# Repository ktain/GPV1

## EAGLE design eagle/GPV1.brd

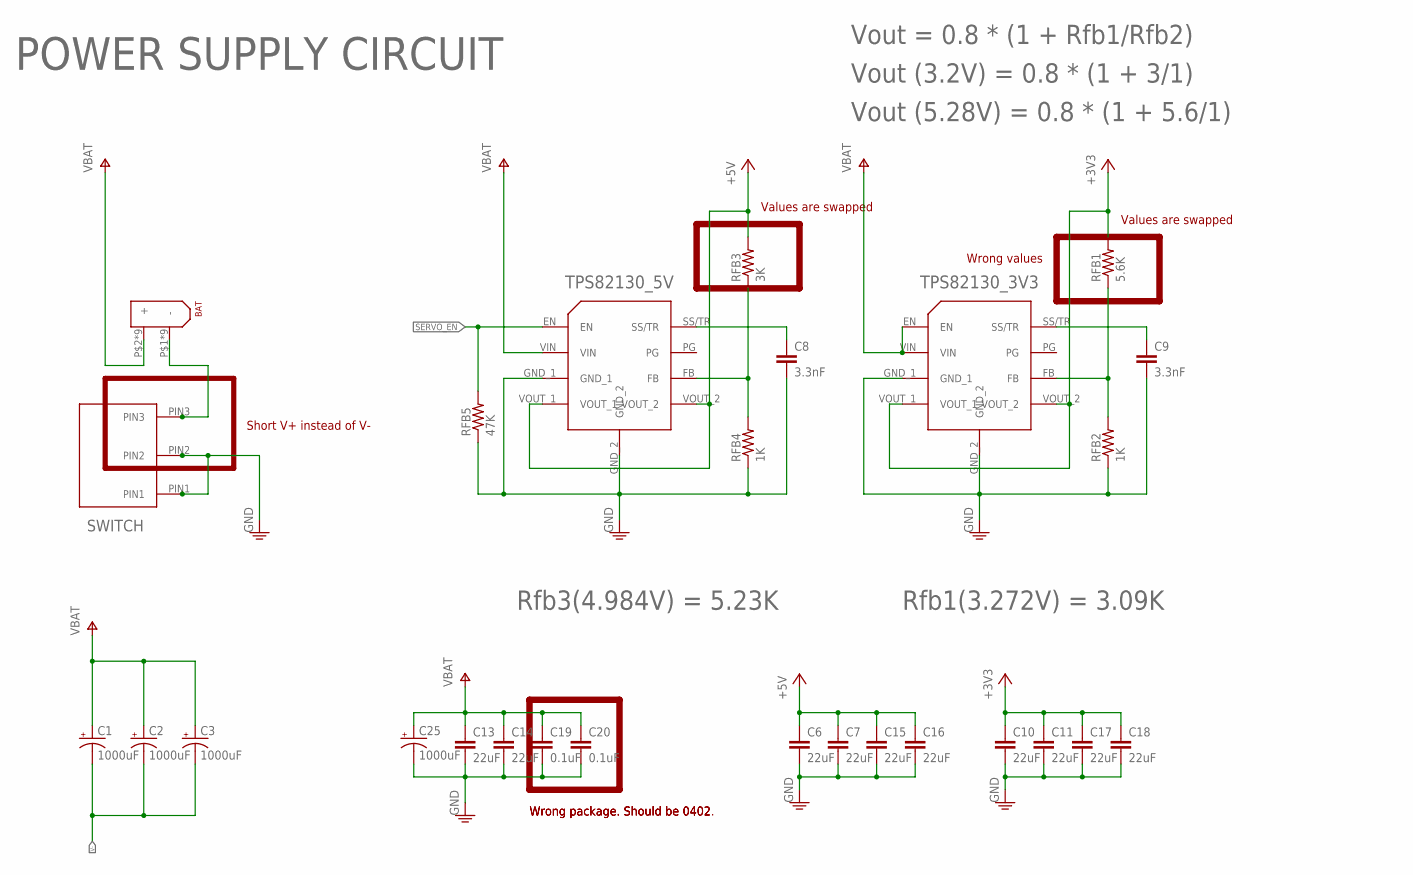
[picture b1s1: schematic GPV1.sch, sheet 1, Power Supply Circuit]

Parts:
BAT: XT-60
C1, C2, C3, C25: 1000uF; PANASONIC_H13
C6, C7, C10, C11, C13, C14, C15, C16, C17, C18: 22uF; 0805
C8, C9: 3.3nF; 0402-CAP
C19, C20: 0.1uF; 0805
ON<-->OFF: TS02_SWITCH
RFB1: 5.6K; 0402-RES
RFB2, RFB4: 1K; 0402-RES
RFB3: 3K; 0402-RES
RFB5: 47K; 0402-RES
TPS82130_3V3, TPS82130_5V: TPS82130

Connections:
+3V3: C10.1, C11.1, C17.1, C18.1, RFB1.2, TPS82130_3V3.VOUT_1, TPS82130_3V3.VOUT_2; also elsewhere on the board
+5V: C6.1, C7.1, C15.1, C16.1, RFB3.2, TPS82130_5V.VOUT_1, TPS82130_5V.VOUT_2; also elsewhere on the board
GND: C6.2, C7.2, C8.2, C9.2, C10.2, C11.2, C13.2, C14.2, C15.2, C16.2, C17.2, C18.2, C19.2, C20.2, C25.-, ON<-->OFF.PIN1, ON<-->OFF.PIN2, RFB2.1, RFB4.1, RFB5.1, TPS82130_3V3.GND_1, TPS82130_3V3.GND_2, TPS82130_5V.GND_1, TPS82130_5V.GND_2; also elsewhere on the board
unnamed: C9.1, TPS82130_3V3.SS/TR
unnamed: RFB1.1, RFB2.2, TPS82130_3V3.FB
unnamed: C8.1, TPS82130_5V.SS/TR
unnamed: RFB3.1, RFB4.2, TPS82130_5V.FB
SERVO_EN: RFB5.2, TPS82130_5V.EN; also elsewhere on the board
V+: BAT.P$2 (+), BAT.P$7 (+), BAT.P$8 (+), BAT.P$9 (+), BAT.P$10 (+), BAT.P$11 (+), BAT.P$12 (+), BAT.P$13 (+), BAT.P$14 (+), C1.+, C2.+, C3.+, C13.1, C14.1, C19.1, C20.1, C25.+, TPS82130_3V3.EN, TPS82130_3V3.VIN, TPS82130_5V.VIN; also elsewhere on the board
V-: BAT.P$1 (-), BAT.P$3 (-), BAT.P$4 (-), BAT.P$5 (-), BAT.P$6 (-), BAT.P$15 (-), BAT.P$16 (-), BAT.P$17 (-), BAT.P$18 (-), C1.-, C2.-, C3.-, ON<-->OFF.PIN3; also elsewhere on the board

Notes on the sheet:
POWER SUPPLY CIRCUIT
Vout = 0.8 * (1 + Rfb1/Rfb2)
Rfb3(4.984V) = 5.23K
Rfb1(3.272V) = 3.09K
Short V+ instead of V-
Wrong package. Should be 0402
Wrong values
Values are swapped
Wrong package. Should be 0402.
Vout (3.2V) = 0.8 * (1 + 3/1)
Vout (5.28V) = 0.8 * (1 + 5.6/1)

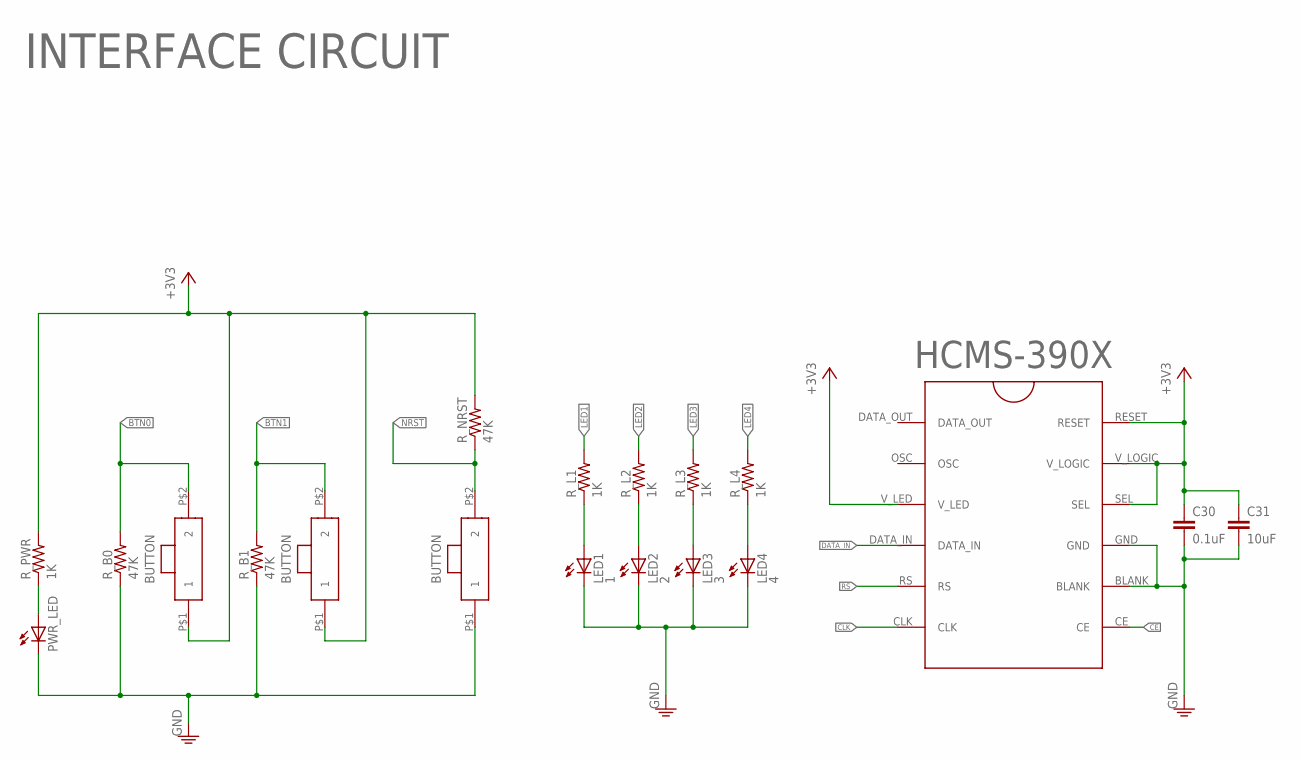
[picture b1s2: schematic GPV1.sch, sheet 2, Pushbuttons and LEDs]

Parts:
BTN0, BTN1: POLOLU_BUTTON
C30: 0.1uF; 0402-CAP
C31: 10uF; 0402-CAP
HCMS-390X: HCMS-390X; HCMS-2903
LED1: 1; LED-0603
LED2: 2; LED-0603
LED3: 3; LED-0603
LED4: 4; LED-0603
PWR_LED: LED0603; LED-0603
RESET: NRST; POLOLU_BUTTON
R_B0, R_B1: 47K; 0402-RES
R_L1, R_L2, R_L3, R_L4: 1K; 0402-RES
R_NRST: 47K; 0402-RES
R_PWR: 1K; 0402-RES

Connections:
+3V3: BTN0.P$1 (1), BTN1.P$1 (1), C30.1, C31.1, HCMS-390X.RESET, HCMS-390X.SEL, HCMS-390X.V_LED, HCMS-390X.V_LOGIC, R_NRST.2, R_PWR.2; also elsewhere on the board
BTN0: BTN0.P$2 (2), R_B0.2; also elsewhere on the board
BTN1: BTN1.P$2 (2), R_B1.2; also elsewhere on the board
CE: HCMS-390X.CE; also elsewhere on the board
CLK: HCMS-390X.CLK; also elsewhere on the board
DATA_IN: HCMS-390X.DATA_IN; also elsewhere on the board
GND: C30.2, C31.2, HCMS-390X.BLANK, HCMS-390X.GND, LED1.C, LED2.C, LED3.C, LED4.C, PWR_LED.C, RESET.P$1 (1), R_B0.1, R_B1.1; also elsewhere on the board
LED1: R_L1.2; also elsewhere on the board
LED2: R_L2.2; also elsewhere on the board
LED3: R_L3.2; also elsewhere on the board
LED4: R_L4.2; also elsewhere on the board
unnamed: PWR_LED.A, R_PWR.1
unnamed: LED1.A, R_L1.1
unnamed: LED2.A, R_L2.1
unnamed: LED3.A, R_L3.1
unnamed: LED4.A, R_L4.1
NRST: RESET.P$2 (2), R_NRST.1; also elsewhere on the board
RS: HCMS-390X.RS; also elsewhere on the board

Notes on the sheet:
INTERFACE CIRCUIT

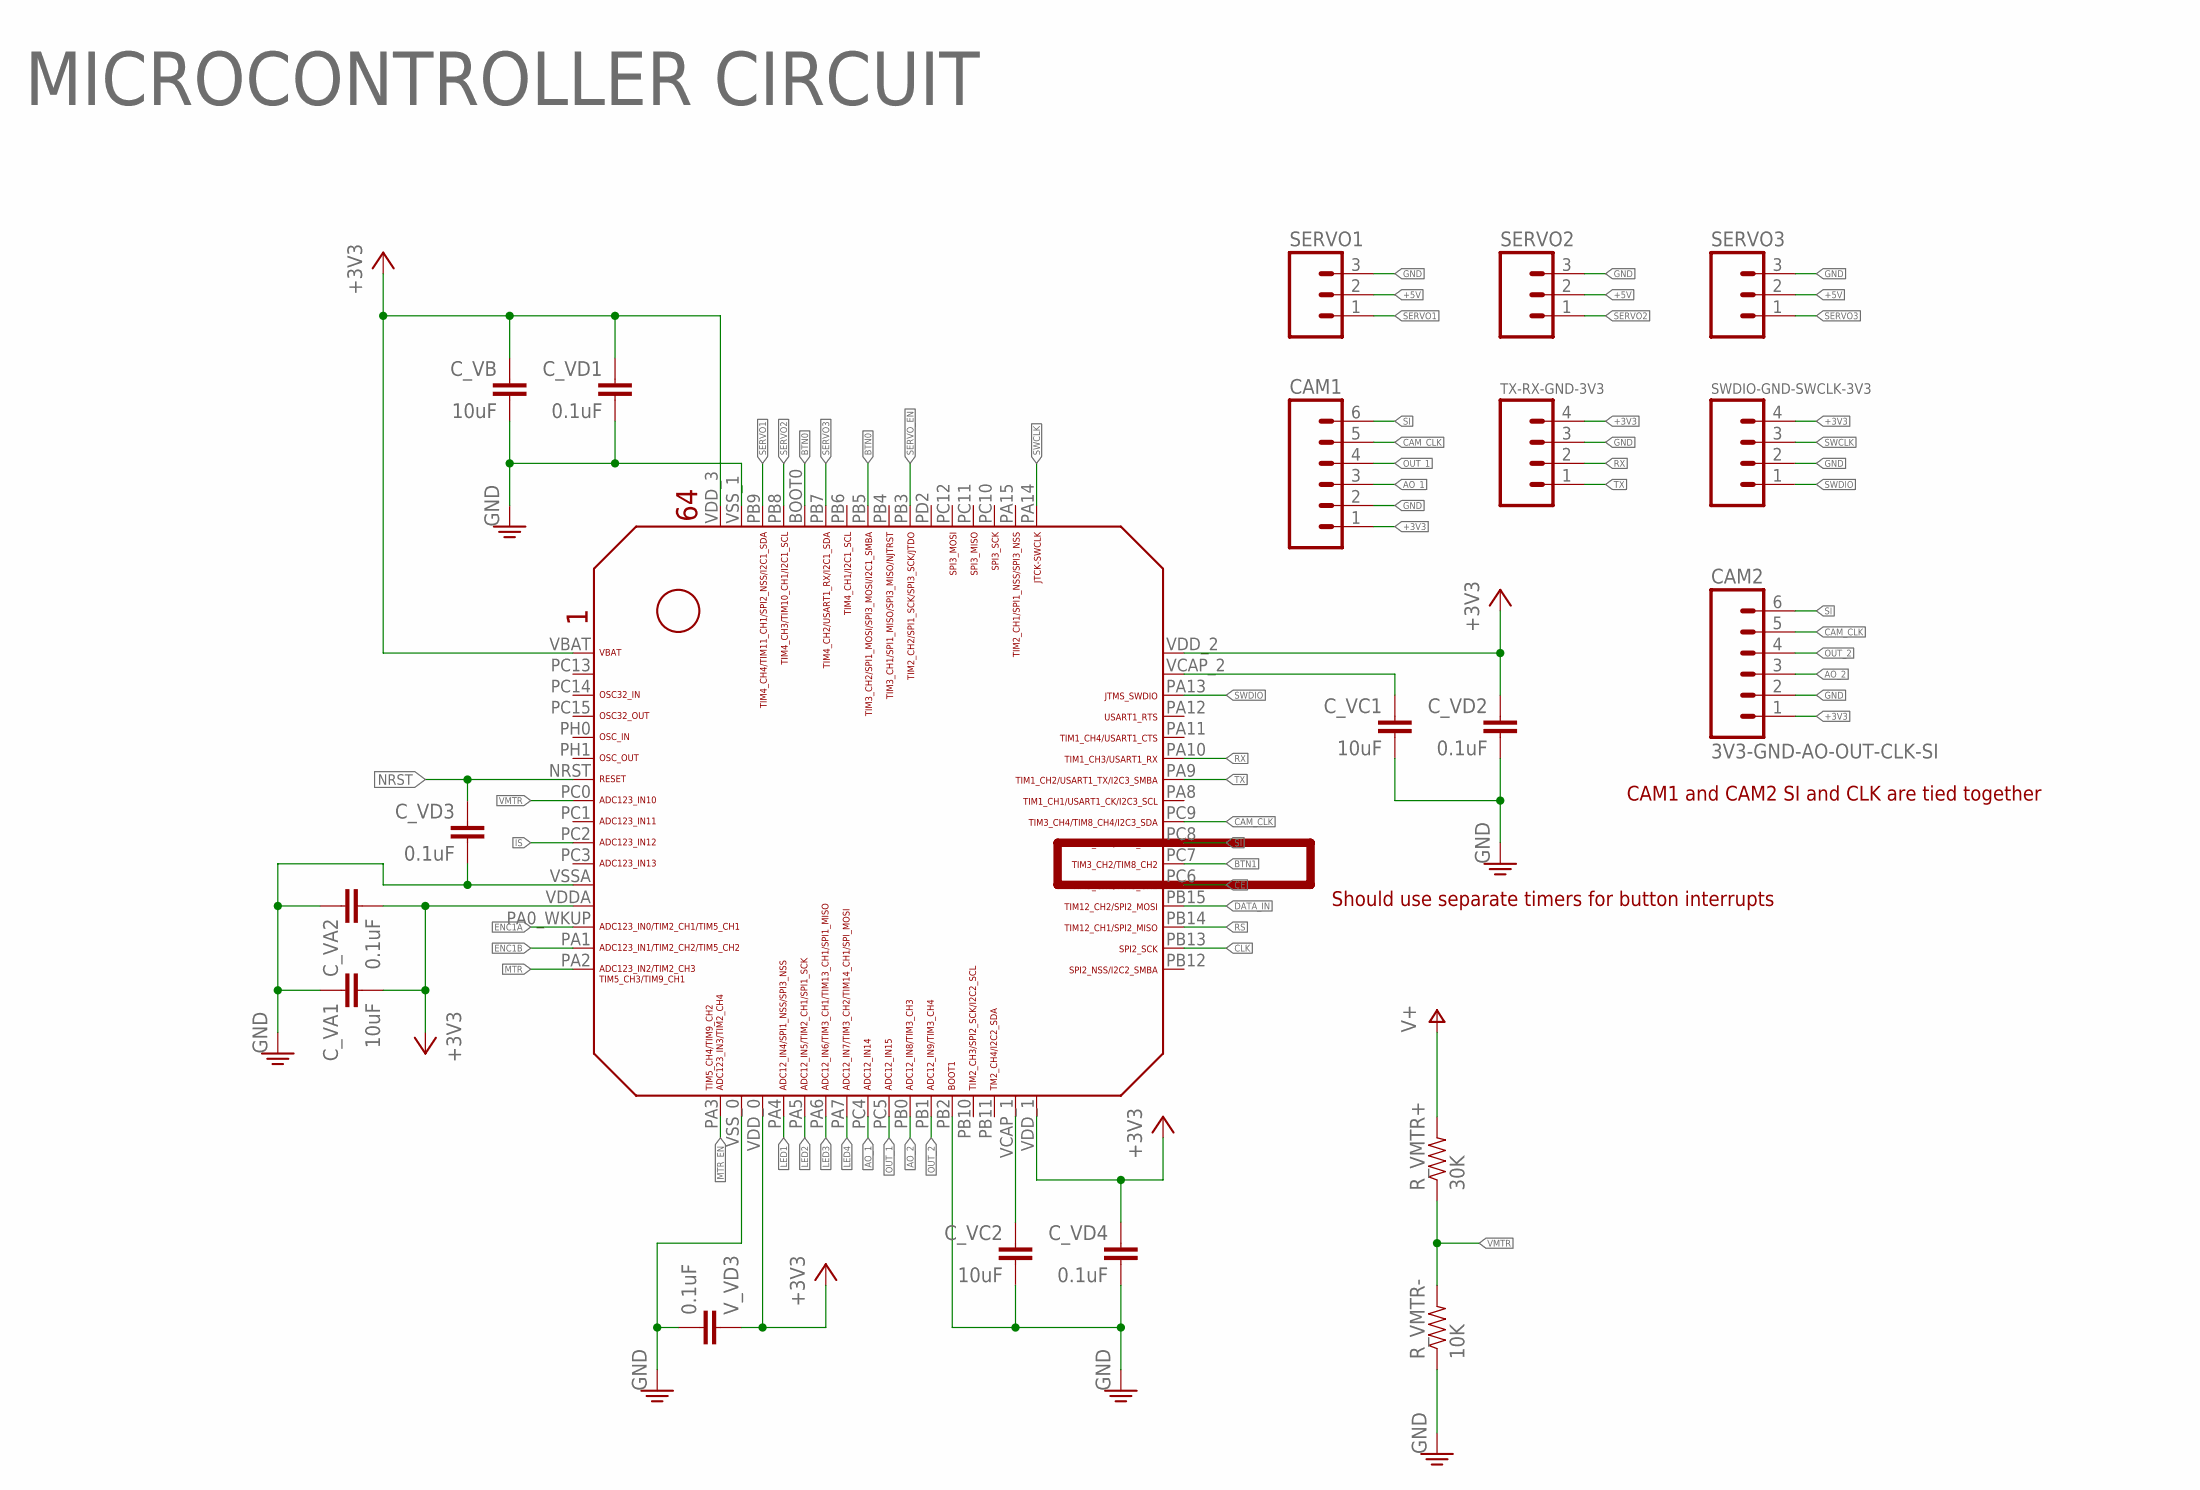
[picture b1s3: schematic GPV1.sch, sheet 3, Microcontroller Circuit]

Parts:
CAM1: M06SIP; 1X06
CAM2: 3V3-GND-AO-OUT-CLK-SI; 1X06
C_VA1: 10uF; 0402-CAP
C_VA2: 0.1uF; 0402-CAP
C_VB: 10uF; 0402-CAP
C_VC1, C_VC2: 10uF; 0402-CAP
C_VD1, C_VD2, C_VD3, C_VD4: 0.1uF; 0402-CAP
R_VMTR+: 30K; 0402-RES
R_VMTR-: 10K; 0402-RES
SERVO1, SERVO2, SERVO3: M03PTH; 1X03
STM32F4X5RG: STM32F405/415_LQFP64
SWDIO-GND-SWCLK-3V3: M04PTH; 1X04
TX-RX-GND-3V3: M04PTH; 1X04
V_VD3: 0.1uF; 0402-CAP

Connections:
+3V3: CAM1.1, CAM2.1, C_VA1.2, C_VA2.2, C_VB.1, C_VD1.1, C_VD2.1, C_VD4.1, STM32F4X5RG.VBAT, STM32F4X5RG.VDDA, STM32F4X5RG.VDD_0, STM32F4X5RG.VDD_1, STM32F4X5RG.VDD_2, STM32F4X5RG.VDD_3, SWDIO-GND-SWCLK-3V3.4, TX-RX-GND-3V3.4, V_VD3.1; also elsewhere on the board
+5V: SERVO1.2, SERVO2.2, SERVO3.2; also elsewhere on the board
AO_1: CAM1.3, STM32F4X5RG.PC4
AO_2: CAM2.3, STM32F4X5RG.PB0
BTN0: STM32F4X5RG.BOOT0, STM32F4X5RG.PB5; also elsewhere on the board
BTN1: STM32F4X5RG.PC7; also elsewhere on the board
CAM_CLK: CAM1.5, CAM2.5, STM32F4X5RG.PC9
CE: STM32F4X5RG.PC6; also elsewhere on the board
CLK: STM32F4X5RG.PB13; also elsewhere on the board
DATA_IN: STM32F4X5RG.PB15; also elsewhere on the board
ENC1A: STM32F4X5RG.PA0_WKUP (PA0_AKUP); also elsewhere on the board
ENC1B: STM32F4X5RG.PA1; also elsewhere on the board
GND: CAM1.2, CAM2.2, C_VA1.1, C_VA2.1, C_VB.2, C_VC1.2, C_VC2.2, C_VD1.2, C_VD2.2, C_VD3.2, C_VD4.2, R_VMTR-.1, SERVO1.3, SERVO2.3, SERVO3.3, STM32F4X5RG.PB2, STM32F4X5RG.VSSA, STM32F4X5RG.VSS_0, STM32F4X5RG.VSS_1, SWDIO-GND-SWCLK-3V3.2, TX-RX-GND-3V3.3, V_VD3.2; also elsewhere on the board
IS: STM32F4X5RG.PC2; also elsewhere on the board
LED1: STM32F4X5RG.PA4; also elsewhere on the board
LED2: STM32F4X5RG.PA5; also elsewhere on the board
LED3: STM32F4X5RG.PA6; also elsewhere on the board
LED4: STM32F4X5RG.PA7; also elsewhere on the board
MTR: STM32F4X5RG.PA2; also elsewhere on the board
MTR_EN: STM32F4X5RG.PA3; also elsewhere on the board
unnamed: C_VC2.1, STM32F4X5RG.VCAP_1
unnamed: C_VC1.1, STM32F4X5RG.VCAP_2
NRST: C_VD3.1, STM32F4X5RG.NRST; also elsewhere on the board
OUT_1: CAM1.4, STM32F4X5RG.PC5
OUT_2: CAM2.4, STM32F4X5RG.PB1
RS: STM32F4X5RG.PB14; also elsewhere on the board
RX: STM32F4X5RG.PA10, TX-RX-GND-3V3.2
SERVO1: SERVO1.1, STM32F4X5RG.PB9
SERVO2: SERVO2.1, STM32F4X5RG.PB8
SERVO3: SERVO3.1, STM32F4X5RG.PB7
SERVO_EN: STM32F4X5RG.PB3; also elsewhere on the board
SI: CAM1.6, CAM2.6, STM32F4X5RG.PC8
SWCLK: STM32F4X5RG.PA14, SWDIO-GND-SWCLK-3V3.3
SWDIO: STM32F4X5RG.PA13, SWDIO-GND-SWCLK-3V3.1
TX: STM32F4X5RG.PA9, TX-RX-GND-3V3.1
V+: R_VMTR+.2; also elsewhere on the board
VMTR: R_VMTR+.1, R_VMTR-.2, STM32F4X5RG.PC0

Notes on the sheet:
MICROCONTROLLER CIRCUIT
Should use separate timers for button interrupts
CAM1 and CAM2 SI and CLK are tied together

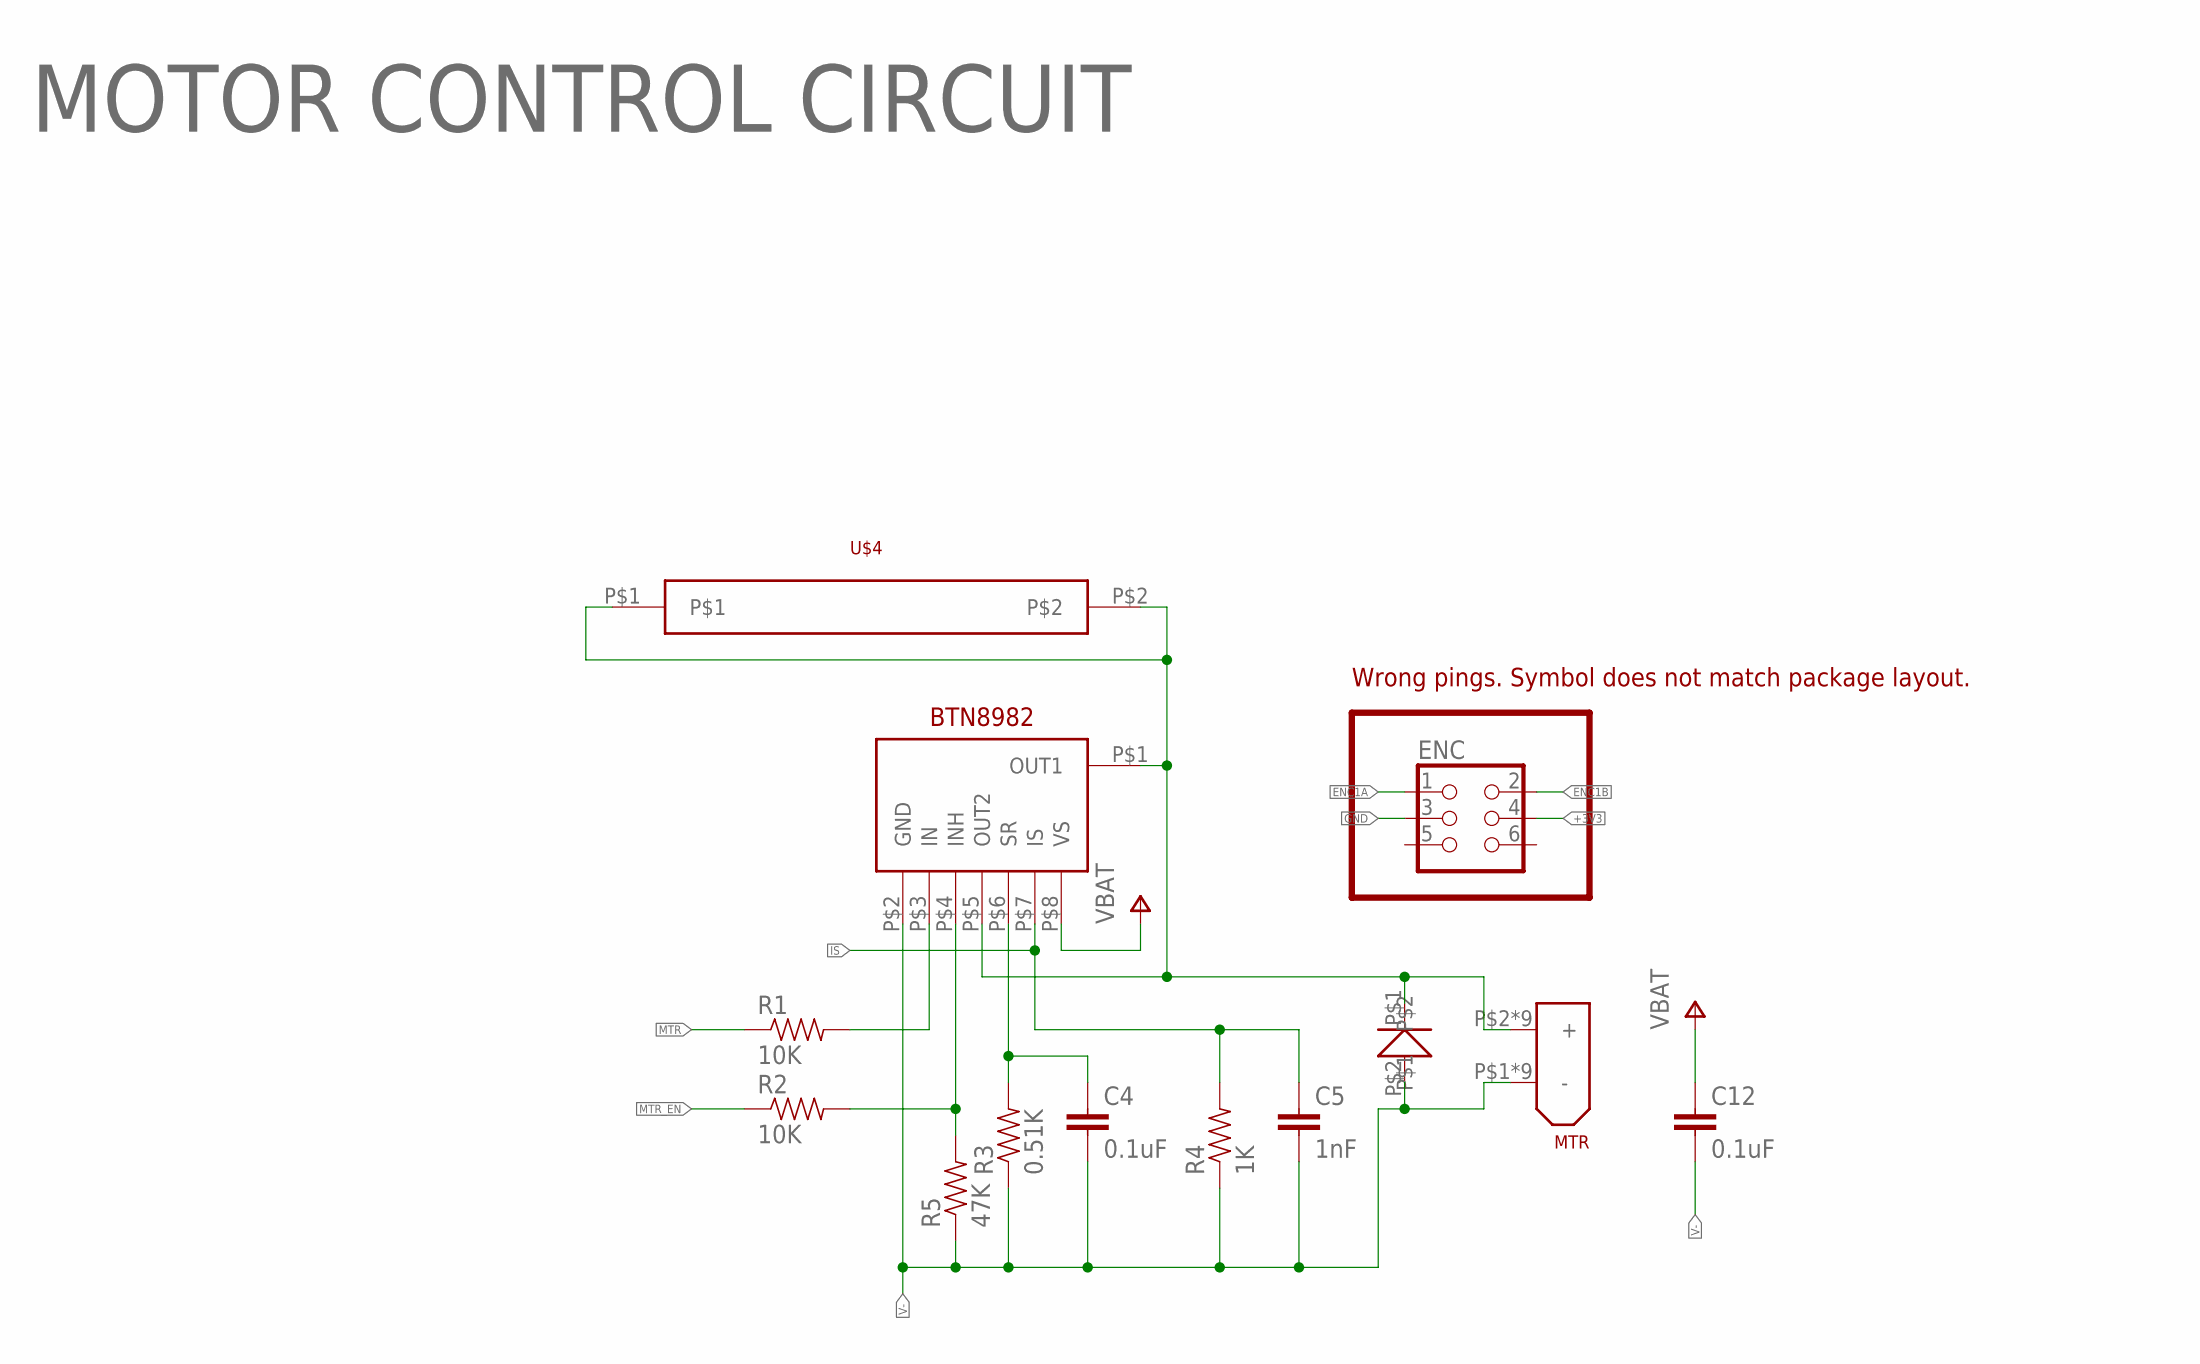
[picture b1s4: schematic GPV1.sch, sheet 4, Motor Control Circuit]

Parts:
BTN8982: BTN8982
C4, C12: 0.1uF; 0402-CAP
C5: 1nF; 0402-CAP
DIODE: DIODE_DO-214AB; DO-214AB
ENC: PINHD-2X31; DIN-41651
MTR: XT-60
R1, R2: 10K; 0402-RES
R3: 0.51K; 0402-RES
R4: 1K; 0402-RES
R5: 47K; 0402-RES
U$4: HEATSINK_TO-263

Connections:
+3V3: ENC.4; also elsewhere on the board
ENC1A: ENC.1; also elsewhere on the board
ENC1B: ENC.2; also elsewhere on the board
GND: ENC.3; also elsewhere on the board
IS: BTN8982.P$7 (IS), C5.1, R4.2; also elsewhere on the board
MTR: R1.1; also elsewhere on the board
MTR_EN: R2.1; also elsewhere on the board
unnamed: BTN8982.P$3 (IN), R1.2
unnamed: BTN8982.P$4 (INH), R2.2, R5.2
unnamed: BTN8982.P$6 (SR), C4.1, R3.2
unnamed: BTN8982.P$1 (OUT1), BTN8982.P$5 (OUT2), DIODE.P$1, MTR.P$2 (+), MTR.P$7 (+), MTR.P$8 (+), MTR.P$9 (+), MTR.P$10 (+), MTR.P$11 (+), MTR.P$12 (+), MTR.P$13 (+), MTR.P$14 (+), U$4.P$1, U$4.P$2
V+: BTN8982.P$8 (VS), C12.1; also elsewhere on the board
V-: BTN8982.P$2 (GND), C4.2, C5.2, C12.2, DIODE.P$2, MTR.P$1 (-), MTR.P$3 (-), MTR.P$4 (-), MTR.P$5 (-), MTR.P$6 (-), MTR.P$15 (-), MTR.P$16 (-), MTR.P$17 (-), MTR.P$18 (-), R3.1, R4.1, R5.1; also elsewhere on the board

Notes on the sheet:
MOTOR CONTROL CIRCUIT
Wrong pings. Symbol does not match package layout.

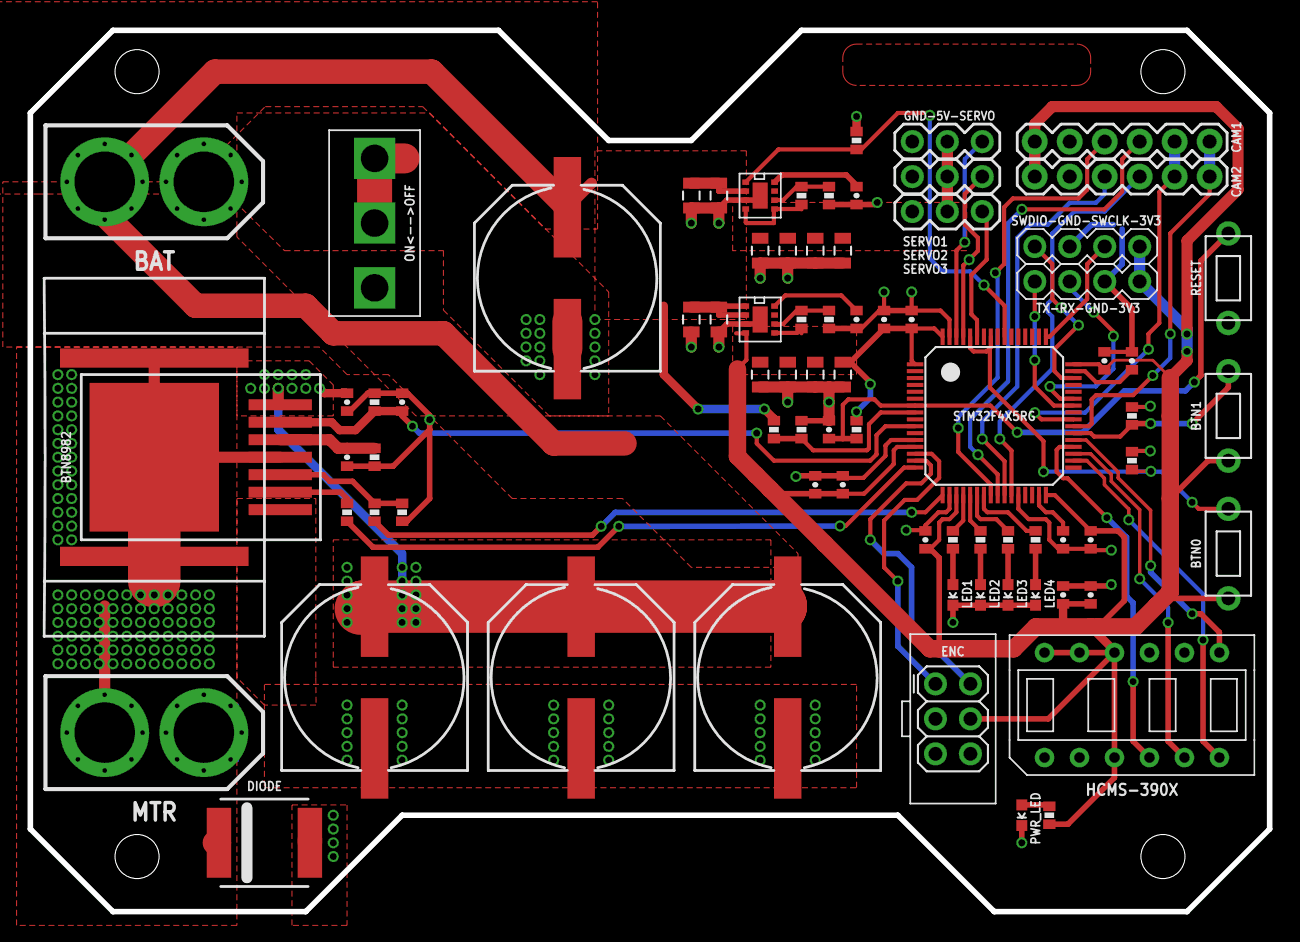
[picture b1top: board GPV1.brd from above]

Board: 2 copper layers, 90.0 x 64.0 mm, 79 parts (0 on the bottom side), 51 nets.

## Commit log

2017-10-20 Initial commit. Most setup routines done. Speed control, servos, camera working.
2017-10-20 Refactored code. Added header comments.
2017-10-21 Implemented display functionality. Fixed static text bug.
2017-10-21 Disabled timer_setup()
2017-10-21 Implemented line tradking graph in python
2017-10-22 Implemented preliminary kill switch functionality in systick
2017-10-23 Removed integration interval. Now reads continously.
2017-10-23 Simulate line tracking in python using raw values
2017-10-23 Refactored code, renamed variables, removed usused code.
2017-10-23 Renamed camera variables
2017-10-23 Renamed lineIndex to linePos, a float
2017-10-23 Implemented spatial moving average filter
2017-10-23 Implemented nearest peak detection in python
2017-10-23 Refactoring
2017-10-23 Added automatic exposure time adjustment
2017-10-25 Added eagle board and schematic
2017-10-25 Added GPV1-specific eagle libraries
2017-10-25 Corrected feedback resistor notes in schematic.
2017-10-26 Fixed nearest peak relative to old position (python). Added max line width.
2017-10-26 Added nearest peak detection (C)
2017-10-27 Fixed nearest peak detection.
2017-10-27 Refactored steering code. Adjustable servo period.
2017-10-27 Modified getNearestPeak for floating point operation. Servos stable at 3000us (333Hz)
2017-10-27 Added legend to python plot.
2017-10-27 Declared min and max line width as global variables. detectLinePos and getNearestPeak now operate on a pointer to a pixel array.
2017-10-27 Added min and max exposure time limits
2017-10-30 Camera read routine moved to TIM3 interrupt
2017-10-30 Changed camera read order to STOP->RESTART->SAVE
2017-10-30 Automatic exposure time adjustment using TIM3->ARR
2017-10-30 Steering PD implemented
2018-05-03 Fixed display with less than 4 characters
2018-05-03 Added ticks per option setting
2018-05-03 Added speed profiles and adjustable camera tilt angle to menu
2018-05-03 Speedup along straights

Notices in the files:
parts and their libraries:
SPARKFUN: Licensing: CC v3.0 Share-Alike You are welcome to use this library for commercial purposes.
